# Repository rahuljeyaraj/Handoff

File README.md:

# Handoff

**Shake hands. Share contacts.**

Two people wear a wristband. They shake hands, and their contact cards cross
between the bands **through the two bodies** and land in each other's phones. No
cards, no QR codes, no spelling a name out.

The body is the wire. A coated metal plate on the back of each band couples a
pair of tones into the skin at 180 and 200 kHz, the handshake joins the two
arms, and the plate on the other band picks up what survives. Capacitive
body-coupled communication, at 0 cm.

**[Read the full write-up, with figures](docs/element14-blog.md)** is the place
to start. It is the project end to end: what it feels like to use, how the link
works, the two physical layers, and two appendices that get you from an empty
desk to a working pair.

Built for element14's **Make a Connection** contest. The PCBs were sponsored by
[PCBWay](https://www.pcbway.com/).

---

## What is here

A finished pair of bands, and everything that made them.

| | |
|---|---|
| **Firmware** | `firmware/` one C image per milestone, Pico SDK, host-testable DSP and protocol |
| **Board** | `hardware/` KiCad 10, generated from a script, fabrication zip ready to upload |
| **Box** | `hardware/enclosure/` two printed halves, 22 mm strap |
| **App** | `android/` native Android: pairing, provisioning, history, notes |
| **Docs** | `docs/` the write-up, the design, the radio, bring-up |

## Where to go next

| I want to | Read |
|---|---|
| understand the whole thing | [docs/element14-blog.md](docs/element14-blog.md) |
| build a pair myself | appendices A and B of the same file, then [docs/hardware-bringup.md](docs/hardware-bringup.md) |
| know why the electrical design is what it is | [docs/body-coupled-handshake-design.md](docs/body-coupled-handshake-design.md) |
| know how the radio works today | [docs/link-v2-design.md](docs/link-v2-design.md) |
| know what v1 got wrong, and why it matters | appendix C of the write-up |
| find my way round the firmware | [docs/firmware-architecture.md](docs/firmware-architecture.md) |
| work on the board | [hardware/README.md](hardware/README.md) |
| work on the app | [android/README.md](android/README.md) |

---

## Status

Both bands are built, boxed, worn and working. The link on `main` is **v2**, the
second physical layer. v1 is kept only as appendix C of the write-up, because
its mistakes are the reason v2 looks the way it does.

**Measured**

* Two bands complete handshakes continuously through a real skin path, on their
  own cells, with nothing tethered.
* Worn link test, v2: **1015 good frames, frame error rate 0.163**, against
  v1's 447 and 0.296 on the same bench. About twice as good.
* Bands apart at the same spacing, v1: **nothing gets through**. That is the
  measurement that says the path is the body and not the air.
* Host suite: **25 868 checks**, all green, in a couple of seconds, no hardware.
* Every bring-up step on both boards, with a multimeter. No oscilloscope was
  used anywhere in this project.

**Not measured, and worth saying so**

* Current draw, and so battery life. Both cores run flat out all day and nothing
  sleeps.
* Two bands within about 10 cm complete a handshake with nobody holding either
  of them. That is a near-field leak, not the intent.
* The band has to be on the hand that shakes. The other wrist does not work, and
  nothing in the design says why.

Chapter 7 of the write-up is the full list of what the next pair should do
better.

---

## How the link works, in one screen

| | |
|---|---|
| Tones | 180 kHz and 200 kHz, one on the plate at all times, straight out of a PIO pin |
| Bit | two chips, Manchester: low then high is a 0, high then low is a 1 |
| Rate | 4000 chips a second, so **2000 bits a second** |
| Receiver | ADC free-running at 500 ksps into a DMA ring; core 1 runs five Goertzel filters over every 25 samples |
| Window | 50 us, 20 000 a second, five windows to a chip |
| Decision | which of the two tones was louder. Never how loud |
| Guard bins | 140, 160 and 220 kHz, pitches nobody ever sends, measured through the same body and the same amplifier |
| Presence | the tone against the **median of those three**, by a margin computed from "one false busy a minute". Cell-averaging CFAR, not a tracked floor |
| Sync | no chip count: find the one `00` in the preamble, then check 28 of the 30 transitions around it |
| Frame | fixed size, 156 ms, CRC-16/CCITT. No length field |
| Card | a vCard packed from 169 bytes to 79, cut into frames most important first |
| Rendezvous | every band beacons a nonce, then listens for a random time. Being heard is the touch |
| Turn taking | the band that **heard** sends first, then one frame each, plain round robin |
| Clock | 144 MHz, not the SDK's 150, so both tone periods are a whole even number of cycles |

Not one of those numbers was tuned on the bench. Each comes from a requirement
sentence and arithmetic, and the host suite asserts the arithmetic.

---

## Hardware

| | |
|---|---|
| MCU board | Raspberry Pi Pico 2 W (RP2350 + CYW43439), socketed, not soldered |
| Why RP2350 | RP2040 has a known ADC differential-non-linearity defect |
| Why the W | BLE is the link from the band to its owner's phone |
| Why a Pico at all | PIO makes both tones with no oscillator and no driver chip, and leaves both cores for the work |
| Analogue | MCP6292 dual rail-to-rail op-amp, two stages of x11 |
| Electrodes | two 25 x 25 mm copper-clad squares: the taped skin plate, and an outer one tied to board ground that couples to the room |
| Power | 1S LiPo, about 500 mAh, charged on an off-board TP4056. The Pico's own buck-boost takes the cell from 4.2 V down past 3.0 V |
| Wearer UI | one RGB LED, one coin vibration motor, one button, one slide switch |
| Board | 40 x 62 mm, 2 layers, 1.6 mm. `hardware/build/handoff-pcbway.zip` is ready to upload |
| Box | about 45 x 65 x 25 mm, on a 22 mm strap |

> ### Safety is not optional
>
> **Battery only, both ends, whenever anyone is wearing one.** Never on a
> mains-powered laptop. A tethered reading is also a *wrong* reading: the USB
> lead joins the two bands' grounds through the PC, and that return path is the
> thing under test.
>
> **Every electrode is insulated**, edge to edge, and the skin plate is never
> bare. **Hand to hand only**, and **nobody with a pacemaker or an implanted
> defibrillator.**
>
> The series resistors fitted are **100 kOhm**, which holds the worst-case
> current through a person under **33 uA**, with the insulation on top of that.
> The design document's rule is 1 MOhm, ten times less again, and the silkscreen
> and `hardware/bom.csv` still say so. Appendix B.1 of the write-up is the whole
> justification for the deviation.
>
> Read section 13 of
> [docs/body-coupled-handshake-design.md](docs/body-coupled-handshake-design.md)
> before powering anything on a wrist.

---

## Layout

```
CMakeLists.txt            top level; PICO_BOARD=pico2_w, 144 MHz, handoff_add_app()
pico_sdk_import.cmake     stock SDK bootstrap, from pico-sdk 2.3.1

firmware/
  apps/                   one flashable image per milestone
    blink/                board, toolchain and USB console alive
    txgen/                tone generation, self-measured
    adcbench/             the 500 ksps DMA ring and the Goertzel budget
    loopback/             the whole link inside one chip
    linktest/             one-way link between two boards
    turnaround/           half duplex: how fast a band can swap direction
    afe_sweep/            the analogue front end, characterised alone
    bringup/              the PCB bring-up image, driven by scripts/bringup.py
    handoff/              the real thing, plus the LED, motor and wear logic
  lib/
    dsp/                  Goertzel, the FSK decision, CFAR presence, chip sync
    link/                 Manchester, framing, CRC-16, phone-link chunking
    record/               vCard codec, compact TLV, fragmentation, flash store
    proto/                beacon and rendezvous, the exchange, the carousel
    ui/                   the LED vocabulary and the button
    hal/                  the seam: interfaces and config.h, no code
    hal_pico/             the RP2350 binding: PIO, ADC ring, BLE, flash, IPC
  test/
    host/                 unit tests, channel simulator, two-node protocol sim
    vectors/generated/    from tools/gen_vectors.py, derived, git-ignored
    vectors/captures/     from hardware, committed, replayed forever

scripts/build.py          build and flash the firmware        (Windows + Linux)
scripts/test.py           build and run the host tests        (Windows + Linux)
scripts/bringup.py        the PCB bring-up driver: flash, then LED, motor, TX
scripts/link2.py          one process, two boards' consoles, one timeline
scripts/blelog.py         band readings off two phones by radio, never over USB
tools/                    vector generator, reference vCard codec, plotter, labels
hardware/                 the KiCad project, its generators, the fab zip, the box
android/                  the app. Its own Gradle project
docs/                     design, redesign, bring-up, the write-up and its figures
```

Each app is a directory under `firmware/apps/` whose `CMakeLists.txt` ends in
`handoff_add_app(<target>)`. That wrapper exists because the SDK reads the
`.uf2` path from `ARCHIVE_OUTPUT_DIRECTORY` and the `.elf` path from
`RUNTIME_OUTPUT_DIRECTORY`; setting both keeps every artifact together.

---

## Toolchain

Official Raspberry Pi Pico SDK with CMake and Ninja, not PlatformIO. The
low-level work this project needs is first class in the SDK and second class
everywhere else: PIO tone generation, a free-running ADC at 500 ksps into a DMA
ring, core 1 on five Goertzel filters, BLE over BTstack.

Everything is pinned and lives under `~/.pico-sdk`, deliberately **not** on
PATH:

| Component | Version |
|---|---|
| pico-sdk | 2.3.1 |
| ARM GCC | 15.2.Rel1 (`arm-none-eabi`, 15.2.1) |
| CMake | 4.3.4 |
| Ninja | 1.13.2 |
| picotool | 2.3.1 |

These versions appear in three places that must stay in step: the DO-NOT-EDIT
block in [CMakeLists.txt](CMakeLists.txt), the variables at the top of
[scripts/build.py](scripts/build.py), and the paths in
[.vscode/settings.json](.vscode/settings.json).

**First time on a new machine.** Install the **Raspberry Pi Pico** VS Code
extension (`raspberry-pi.raspberry-pi-pico`), open this folder, and let it
download SDK 2.3.1 when prompted. It populates `~/.pico-sdk` with exactly the
layout above.

## Build

In VS Code, `Ctrl+Shift+B`, or the Pico extension's *Compile Project*. From a
terminal, the same command on Windows and Linux:

```
python scripts/build.py                    # configure + build
python scripts/build.py --clean            # wipe build/ first
python scripts/build.py --flash            # build, then flash over USB
python scripts/build.py --config Release
python scripts/build.py --target handoff   # just one app
python scripts/build.py --help
```

Artifacts land in `build/`: `.uf2`, `.elf`, `.bin`, `.hex`, `.map`, `.dis`.

The script prefers the pinned toolchain under `~/.pico-sdk` and falls back to
whatever is on `PATH`, so a Linux box with distro `cmake`, `ninja` and
`arm-none-eabi-gcc` builds this without the VS Code extension's bundle. Python
3.8 or newer, standard library only.

**For a real band, use the bring-up script instead**, because the PCB moves the
transmitter pin and wants its own build directory:

```
python scripts/bringup.py flash handoff
```

That builds into `build-pcb/` with the board's pin map, flashes it, and can then
drive the LED, the motor and the transmitter from the PC. It is the script
[docs/hardware-bringup.md](docs/hardware-bringup.md) is written against.

## Flash

Either drag a `.uf2` onto the `RP2350` drive that appears when you plug the board
in holding **BOOTSEL**, or use `--flash`. `picotool ... -fx` reboots a running
board into BOOTSEL by itself, so BOOTSEL is only needed for the first flash. On
Linux, install picotool's udev rules rather than running the flash step under
`sudo`.

With two boards on one PC, name the board by its serial rather than its COM
port. The serial is matched as a suffix, so `93D1` finds `4904EF1FFA2393D1`, and
that survives the ports moving.

## Serial console

The firmware presents a USB CDC port. Any terminal at any baud rate works, and
the rate is ignored because it is USB:

```
# Windows: 'mode' lists COM ports; attach with PuTTY or Windows Terminal
# Linux:   /dev/ttyACM0; attach with 'screen /dev/ttyACM0' or 'picocom'
```

For a two-board bench, use `scripts/link2.py` instead of two terminals. It opens
both consoles in one process, stamps every line with the time since the run
started, and can send commands on a schedule. Two separate terminals cannot
answer "which board decided to send first", because their clocks are the
operator's hands.

**Never read a worn band over USB.** Use `scripts/blelog.py`, which takes the
same counters off both phones over BLE while the bands stay floating. A tethered
reading of a body link is wrong, not just unsafe.

---

## Host tests

**Most of this project is testable with no hardware at all**, and that is
structural rather than lucky: nothing under `lib/dsp`, `lib/link`, `lib/record`,
`lib/proto` or `lib/ui` may include a Pico SDK header, so they all compile with a
host compiler and run against a channel simulator.

```
python scripts/test.py                    build and run everything
python scripts/test.py --check            the layering rule only, no compiler
python scripts/test.py --suite frame      one suite
python scripts/test.py --ber              the BER sweep
python scripts/test.py --sweep            the parameter sweeps
python scripts/test.py --define HANDOFF_GZ_N=50
```

A run regenerates the golden vectors from `tools/gen_vectors.py`, cross-checks
the C vCard codec against `tools/vcf.py` in both directions, and executes every
suite. Currently **25 868 checks in a couple of seconds**.

Needs any host C compiler: `gcc` or `clang` if one is on `PATH`, otherwise the
Visual Studio build tools on Windows. This is **separate** from the
`arm-none-eabi` toolchain the firmware uses, and neither substitutes for the
other.

Three rules are worth knowing before changing anything here:

* **Golden vectors are generated from the spec, not from the C encoder**
  (`tools/gen_vectors.py`). If the encoder and decoder share a misreading of the
  frame format, a loopback test passes and the link still fails on the bench. An
  independent generator is the only thing that catches that.
* **Every hardware failure becomes a host test.** A capture that broke the
  decoder on the bench goes into `firmware/test/vectors/captures/` through
  `tools/replay.py --adopt` and is replayed forever. The bug is not fixed until
  it is a regression test.
* **The derived constants are asserted, not trusted.** The tone periods, the
  CFAR margin, the sync threshold and the clock are static-asserted in
  `firmware/lib/hal/config.h` and re-derived in the suite. Changing one number by
  hand fails the build, which is the point.

---

## Two things the design doc gets wrong about the Pico 2 W

Both cost an evening, and both fail silently rather than at build time.

**The SMPS mode pin.** Section 10.4 says tie **GP23** high to force
fixed-frequency PWM. That is right for a plain Pico 2
(`PICO_SMPS_MODE_PIN 23`) and **wrong for the 2 W**: there GP23 drives the CYW43
power enable, and SMPS mode control moves to WL_GPIO1 on the wireless chip,
`cyw43_arch_gpio_put(CYW43_WL_GPIO_SMPS_PIN, true)`.

**The LED.** For the same reason there is no `PICO_DEFAULT_LED_PIN` on a 2 W, so
even blinking needs `cyw43_arch_init()` first.

---

## Thanks

[PCBWay](https://www.pcbway.com/) sponsored and manufactured the boards, and
their engineers caught two real problems in the files before anything was made.
Chapter 9 of the write-up is that story. Thank you to Serene, Tori and Sophia.

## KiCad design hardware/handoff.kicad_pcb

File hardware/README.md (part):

# Handoff — PCB

KiCad 10 project for the wristband board. Companion to
[docs/body-coupled-handshake-design.md](../docs/body-coupled-handshake-design.md);
the schematic implements its §6/§7 netlist with the changes listed under
*Deviations* below.

**Sponsor:** [PCBWay](https://www.pcbway.com/) is fabricating this board.

| File | What |
|---|---|
| `handoff.kicad_pro` / `handoff.kicad_sch` | the project and its single schematic sheet |
| `handoff.kicad_sym` | project symbol library: Pico 2 W and MCP6292 (the stock library has neither) |
| `handoff.pretty/` | project footprints: the SS-12F23G5 slide switch, the 3.4 mm M3 mounting hole with its boss keep-out, and the SOD-123FL diode (KiCad has none) |
| `tools/gen_schematic.py` | **the source of the schematic.** Generates the sheet from the §7 netlist and proves it with `kicad-cli`: ERC, the netlist against `EXPECTED_NETS` pin for pin, and the BOM against the parts table below. Edit this, not the sheet |
| `tools/render.py` | renders `build/handoff.pdf` to `build/sheet.png` so the sheet can be looked at |
| `review.md` | the pre-layout review: every check, its number, its verdict |
| `schematic-prompt.md` | the brief for the next session: the schematic changes the floor plan forces, then layout |
| `tools/gen_sw_footprint.py` | writes `handoff.pretty/SW_Slide_SS-12F23G5`, geometry measured on the physical part |
| `tools/gen_mount_footprint.py` | writes `handoff.pretty/MountingHole_3.4mm_M3_Boss6mm`: 3.4 mm unplated drill plus the 6 mm boss keep-out. The name follows the boss diameter, so the board cannot point at a footprint that is no longer the one described |
| `tools/gen_sod123fl_footprint.py` | writes `handoff.pretty/D_SOD-123FL` for D1/D3, from the PMEG3020ER-TP outline drawing; `--prove` puts it on `build/fp_test.kicad_pcb`, runs DRC and renders it |
| `tools/gen_assembly.py` / `../docs/hardware-bringup/` | the two assembly drawings (each face, fab references, numbered pads, bottom mirrored) that `docs/hardware-bringup.md` is read against |
| `tools/gen_bom.py` / `bom.csv` | the committed BOM: kicad-cli's export plus the **Package** column it cannot produce, derived from each footprint in one place. Called by `gen_schematic.py` after its BOM check |
| `tools/gen_floorplan.py` / `floorplan.svg` | the floor plan: which block sits where in the enclosure, and why. Placement only, no tracks — the **pre-layout** input. **Superseded by the board**: it still draws E1–E10 inboard of their pins, `JP1-JP7`, `TP12`/`TP13` and the 4.5 mm hole positions, none of which exist. Read `gen_pcb.py`'s `PLACE` table for where things actually are |
| `enclosure/` | the box: `bottom.3mf` and `top.3mf`, an initial design, for a 22 mm strap. The board screws into the bottom on four M3 brass inserts |
| `tools/gen_pcb.py` / `handoff.kicad_pcb` | **the source of the board.** Builds it from the schematic's netlist and the floor plan, then proves it with `kicad-cli`: DRC, schematic parity pin for pin, an independent short check, a ground-pour island check, and every pad against every mounting boss. Writes the fab pack last. Edit this, not the `.kicad_pcb` |
| `build/plot/` | the fab pack: Gerbers for every layer, both Excellon drill files with their maps, and the job file. Regenerated on every `gen_pcb.py` run, so it cannot go stale against the board. Not committed (`build/` is ignored) |
| `build/drills.md` | the drill table: every distinct hole, how many, plated or not, and what asks for it |
| `build/handoff-pcbway.zip` / `build/order.md` | **what is actually uploaded.** The zip is the fab pack plus the order sheet; `order.md` is every answer PCBWay's form asks for, written from the board's own numbers, and the list of things to check on their preview. Both regenerated by `gen_pcb.py` |
| `handoff.kicad_dru` | the four custom DRC rules: two tell KiCad about the third dimension it does not model (the Pico is socketed 8.5 mm up; bare pads have no body, but not over a mounting boss), two enforce the layout conventions it will not check unless asked (no right-angle corners, no stub segments). Written by `gen_pcb.py` |

Regenerate and verify after any change (must end `ERC: 0 violation(s), 0 error(s)`,
`0 missing, 0 unexpected` nets, `0 difference(s)` against the parts table, and
`passive packages: 0603` from the BOM writer):

```
python hardware/tools/gen_schematic.py && python hardware/tools/render.py
```

The board is regenerated separately, with KiCad's own Python (it needs `pcbnew`):

```
"C:/Program Files/KiCad/10.0/bin/python.exe" hardware/tools/gen_pcb.py
```

It must end `DRC: 0 error(s)`, `parity 0`, `unrouted 0 item(s)`,
`fab pack: 17 files in build/plot` and `upload pack: build/handoff-pcbway.zip`,
with no `NET`, `OUTSIDE` or `IN BOSS` lines.
Run `gen_schematic.py` first: the board is built from `build/handoff.net`.

---

## Parts — as ordered from robu.in

Every part below is the exact SKU on order. Do not substitute a package
without changing the footprint.

| Ref | Part | Package / mounting | Robu SKU | Qty |
|---|---|---|---|---|
| U1 | Raspberry Pi Pico 2 W | **socketed** in two 1×20 female strips, not soldered to the board | R190344 | 1 |
| — | 2.54 mm 1×40 female single-row header | cut into two 1×20 for the Pico; nothing else uses it now | 555698 | 1 strip |
| U2 | MCP6292-E/MS dual op-amp, 10 MHz | MSOP-8, soldered directly to the board (no DIP adapter on the PCB) | R193529 | 1 |
| R1, R2, R3 | 1 MΩ ±1 % 100 mW 75 V (Uniohm 0603WAF1004T5E) | **0603** | R134792 | 3 |
| R4, R6, R7, R10, R11, R17 | 100 kΩ (104) | **0603** | MakerBazar 1481824519-20P | 6 (pack of 20) |
| R5, R8, R15 | 10 kΩ (103) | **0603** | MakerBazar 1481824531-20P | 3 (pack of 20) |
| R9 | 1.5 kΩ ±1 % 100 mW 75 V (Uniohm 0603WAF1501T5E) | **0603** | R134878 | 1 |
| R12, R13, R14, R16 | 100 Ω (101) | **0603** | MakerBazar 1860310035-20P | 4 (pack of 20) |
| C3 | 100 nF X7R ±10 % 50 V (Samsung CL10B104KB8NNNC) | **0603** | R172322 | 1 |
| C1, C2 | 330 pF **C0G/NP0** ±5 % 100 V (Samsung CL10C331JC8NNNC) | **0603** | R136892 | 2 |
| C4, C5 | 10 µF X5R ±20 % **25 V** (Murata GRM188R61E106MA73D) | **0603**, non-polarised | R144171 | 2 |
| C6 | **DNP** — 330 pF C0G, the C2 part, fitted only if GP11 leakage turns out to matter (see *Deviations*) | **0603** | R136892 | 0 |
| D1 | PMEG3020ER-TP (**Tech Public**), SOD-123FL, 40 V 2 A Schottky — *not* the Nexperia PMEG3020ER, which is SOD-123W | **SOD-123FL**, `handoff:D_SOD-123FL` | R241663 | 1 |
| SW1 | SS-12F23G5 slide switch, SPDT (1P2T), right-angle, 5 mm handle | 3 terminals at 3.0 mm pitch + 2 mounting ears, `handoff:SW_Slide_SS-12F23G5` | R132611 | 1 |
| D2 | RGB LED, common cathode, 5 mm, clear (5-pack) | off-board: solders into J3 or plugs in via a 4-pin XH pigtail | R183455 | 1 |
| SW2 | Tactile push button 6 × 6 × 5 mm, 4 legs | through-hole, `Button_Switch_THT:SW_PUSH_6mm` | 618182 | 1 |
| Q1 | AO3400A N-channel MOSFET, 30 V 5.2 A, 27 mΩ @ 4.5 V | SOT-23 | MakerBazar R209179 | 1 |
| D3 | PMEG3020ER-TP (**Tech Public**), SOD-123FL, 40 V 2 A Schottky, motor flyback — the D1 part | **SOD-123FL**, `handoff:D_SOD-123FL` | R241663 | 1 |
| M1 | Coin vibration motor, 1034, 10 mm disc, ~3 V | off-board: leads solder into J6 | MakerBazar 522260 | 1 |
| J6 | Motor pads, 2 × 2.54 mm through-hole | takes the motor leads direct, or a 2-pin header | — | 1 |
| J1 | JST-XH 2.54 straight 2-pin male (battery) | through-hole | — | 1 |
| J5 | JST-XH 2.54 straight 2-pin male (charger — **one more 2-pin header than before**) | through-hole | — | 1 |
| J2 | JST-XH 2.54 straight 2-pin male (electrodes) | through-hole | — | 1 |
| J3 | JST-XH 2.54 straight 4-pin male (LED), or the LED soldered straight in | through-hole | — | 1 |
| BT1 | 502030 Li-ion 3.7 V 500 mAh | off-board, on a JST-XH pigtail | — | 1 |

Copper only, nothing to buy: 8 solder jumpers JP1–JP8, 8 test pads TP1–TP8, and
4 mounting holes H1–H4 (M3 clearance, 3.4 mm, unplated, each with a 6 mm boss
keep-out).

The 10 MΩ (Robu 574992) bought for R3 is no longer fitted — see *Deviations*. Keep
it: it is the A/B part for the M7 recovery-versus-loss comparison.

**Every passive on the board is 0603** since the 12 Sep 2026 order (see the last
*This session*). The 1206 1 MΩ / 1.5 kΩ / 330 pF / 100 nF (574983, R137563,
R111869, R153721) and the 0805 10 µF (MakerBazar 1491785836-10P) are no longer
fitted anywhere, and nor is the SS220F (Slkor R193098) both diodes were.

Not on the board, by decision: the TP4056 charger (the cell is charged off-board)
and the MSOP-to-DIP adapter (perfboard only).

> JST "XH" is a 2.50 mm pitch family, not 2.54. Over four pins the difference is
> 0.12 mm and the footprint holes absorb it, so the 5 mm LED's 2.54 mm legs go
> straight into J3.

---

## Deviations from the design doc, and why

**D1 in series with VSYS.** The Pico datasheet's own recommendation for a board
that is battery powered but still gets plugged into USB for flashing: the Pico's
internal Schottky ORs VBUS into VSYS, and this external one stops VSYS from
back-driving the battery. It also makes a reversed battery plug harmless (nothing
powers up) instead of destructive. **Now PMEG3020ER-TP (Tech Public, 40 V 2 A,
SOD-123FL)**, the third part in this position after the 1N5819 (DO-41) and the
SS220F (SMB) — see the session logs. Cost: **~0.4 V at 100 mA** (0.41 V typ at
1 A, 0.5 V max at 2 A, from the Tech Public datasheet; its Fig. 4 puts 100 mA at
0.35–0.4 V — there is no 100 mA line item), leaving ~2.9–3.8 V on VSYS from a
3.3–4.2 V cell, against the Pico's 1.8–5.5 V input range. That is 0.45 V better
than the SS220F's ~0.85 V, which was the price of a 200 V rating this board never
needed. Reverse leakage is 2 µA at 10 V, 25 °C.

**A haptic motor was added, on VSYS behind an N-FET.** Not in the design
doc at all — it arrived with this session's parts order. M1 is off-board on
leads into J6; Q1 switches it low-side from GP28, D3 catches the flyback,
R16/R17 are the gate chain. It runs from VSYS rather than the Pico's 3V3
regulator so that 100 mA of pulsed motor current never shares a rail with
the analogue front end. See *This session* below.

**Battery polarity on J1: pin 1 = BAT−, pin 2 = BAT+.** There is no universal
convention for a 2-pin JST battery plug; the one real XH convention is the
balance-lead one, where pin 1 (square pad) is the negative end. The silkscreen
will say so. Verify the pigtail against the silkscreen before the first plug-in —
D1 means getting it wrong costs nothing but a re-pinned plug.

**RGB LED on GP17 / GP18 / GP19 (R / G / B) through 330 Ω.** J3 pin order is
R, K, G, B — the lead order of a standard 5 mm common-cathode RGB LED, longest
leg second — so the LED can be soldered directly. At 3.3 V and 330 Ω the red
runs ~4 mA and green/blue ~1 mA: a status indicator, not a torch.

*Moved one pin up from GP16/17/18 by the floor plan.* J3 sits hard against the
thumb-side edge, parallel to it, opposite the Pico's **thumb row — which is pins
21–40**, not 1–20. With R → GP17 (pin 22), K → GND (pin 23), G → GP18 (pin 24),
B → GP19 (pin 25), J3's four pins face pins 22–25 straight across: four ~7 mm
traces, no crossings, and the LED's legs bend 90° straight into the header with
no pigtail. The cathode lands on a Pico GND pin that is already there, so the
LED's return does not travel.

**Which row is which.** The Pico sits at 180°: USB overhanging the elbow edge
puts the antenna keep-out at the hand end, and it puts **pins 1–20 on the
little-finger row and pins 21–40 on the thumb row.** The floor plan had these
mirrored until the layout session checked the footprint's own pad coordinates
against its USB and antenna zones. Everything that names a Pico pin and a board
position — J3, the TX escape, BTN and ROLE — depends on
getting this right; it is the cheapest thing on the board to verify and the most
expensive to get wrong.

**J2 carries both electrodes: pin 1 = PAD, pin 2 = ground-plane electrode.**
The ground plane does *not* need air contact; it needs area and distance from
the PAD. Inside a box, the board's own ground pour (plus the Pico's) already is a
ground plane facing outward. J2 pin 2 exists so a separate copper-clad sheet can
be added on the outer face of the enclosure — design §15.1 — if measurement
shows the board's pour is too small. Exactly one wire, per §8.4; the connector
is that one point.

**Solder jumpers, all normally OPEN.** Two copper pads 0.3 mm apart, no part;
bridge with a solder blob to connect, wick it off to isolate. Open rather than
cut-to-open because a blob is reversible and a knife cut is not. The price:
**the board does nothing as delivered until the in-line jumpers are bridged**,
which is deliberate — nothing on this board has been tested, so every stage can
be isolated and driven from a test pad on its own. An open jumper is two
separate nets in the netlist oracle.

| | in series with | open, it isolates… | …and the isolated side is driven from | first used |
|---|---|---|---|---|
| JP5 | D1 cathode → VSYS | the whole board from the cell (USB still powers it) | an ammeter across JP5's own two pads reads the board current; a bench supply on pad 2 replaces the cell | M3 bring-up, M11 battery life |
| JP4 | 3V3 → U2 VDD (and the VREF divider) | the analogue side from the Pico's rail | a bench supply / second cell on JP4 pad 2 — the SMPS-noise experiment; an ammeter across JP4 reads U2's current | M7 |
| JP6 | R10/R11/C4 divider → VREF | the bias divider from the amplifiers | an external 1.65 V on JP6 pad 2 | M7 if VREF is suspected |
| JP7 | PAD → R2 | the pad and the transmitter from the receiver | a signal generator on JP7 pad 2 (through R2: the 1 MΩ is still in circuit) | M7 gain / corner / clipping sweeps |
| JP2 | GP11 → R1 | the transmitter from the pad | nothing — leave open and fit C6 instead if GP11 leakage biases the pad (moving TX to another GPIO does not help: every bank-0 pin has E9) | M3 (measure leakage first), M8 |
| JP3 (3-way) | OUT1 / OUT2 → R9 | the ADC from both stages; centre pad → R9, pad 3 ← OUT2 (×121), pad 1 ← OUT1 (×11) | JP3's own pad 3 or pad 1 as a bare output for the scope | M7: blob to pad 3; move it to pad 1 if a noisy hall clips stage 2 (design §15.2) |
| JP1 | R9 → GP26/ADC0 | the ADC pin from the amplifier | JP1 pad 2 directly, as M5 does with its own attenuator; a wire from JP1 pad 2 to any Pico GND pin grounds the ADC for the M4 noise floor | M4/M5 open, M7 bridged |
| JP8 | GP14 → GND | (a strap, not in-line) | — | M6: bridge on one board to set its role; firmware enables GP14's pull-up |

Nothing touches the high-impedance node (R2/R3/U2 pin 3): no jumper, no test
pad. JP7
is on the *pad* side of R2.

**Bring-up order** — the sequence that makes the jumpers pay for themselves:

1. Nothing bridged, no cell. USB in: the Pico runs, M3–M5 need nothing else
   (M5's loopback goes JP2 pad 1 → JP1 pad 2 by wire; JP1 pad 2 to a Pico GND
   pin grounds the ADC for M4).
2. Bridge **JP4** and **JP6**. Read 3.3 V on JP4 pad 2, 1.65 V ±5 % on JP6
   pad 2, 1.65 V on JP3 pads 1 and 3. Anything else on JP3 is a bias problem:
   open JP6 and inject 1.65 V on its pad 2 to split divider from amplifier.
3. Bridge **JP3 centre–pad 3**. Inject on JP7 pad 2 (JP7 still open): gain,
   corner, clipping and noise sweeps of M7, reading JP3 pad 3 with a scope and
   the ADC after bridging **JP1**.
4. Bridge **JP7**. Now the pad is live; M8 with a capacitor from J2 pin 1 to a
   Pico GND pin.
5. Bridge **JP2** *only after* the M3 leakage measurement (below) says the
   pad node stays at 1.65 V with GP11 high-Z. If it does not, fit **C6** instead.
6. Bridge **JP5** last, with the cell on J1; first reading of J1 pin 2 against
   JP5 pad 2 is the D1 drop.

**There are no test pads.** There were thirteen; every one of them sat on the
same net as a solder-jumper pad, a connector pin or a Pico header pin two
millimetres away, and the owner probes with a meter or a scope tip rather than
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
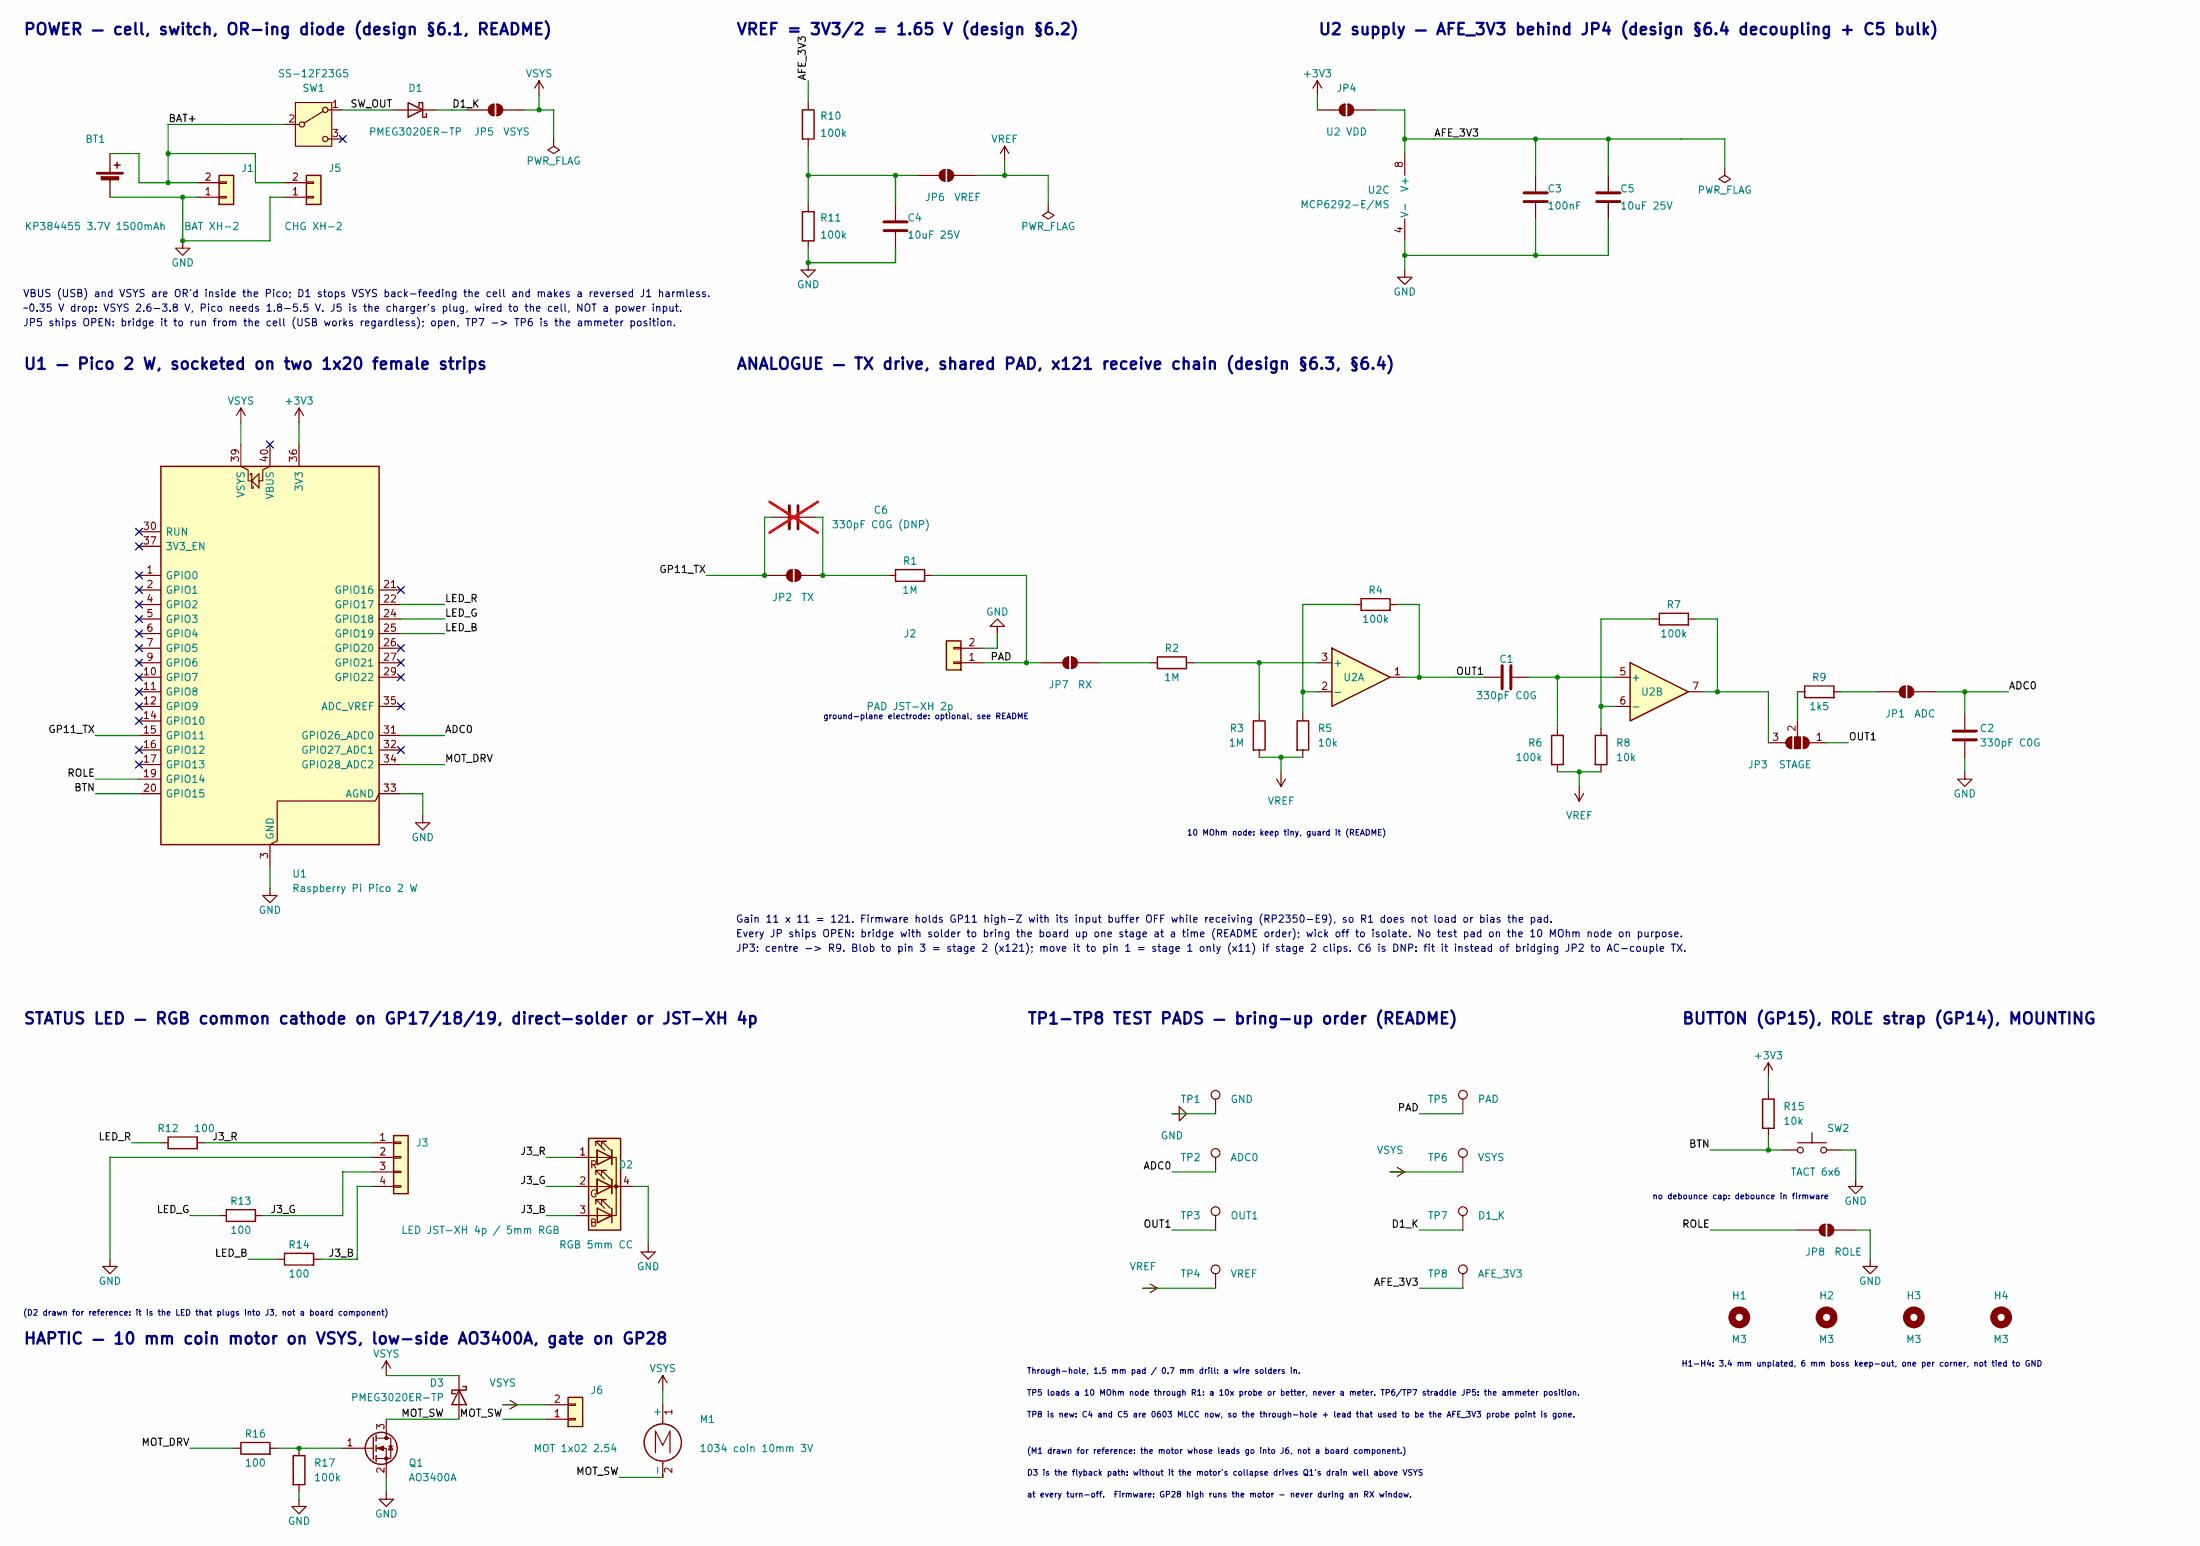
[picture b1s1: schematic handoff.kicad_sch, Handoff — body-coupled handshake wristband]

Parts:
BT1: KP384455 3.7V 1500mAh
C1, C2: 330pF C0G; C_0603_1608Metric_Pad1.08x0.95mm_HandSolder
C3: 100nF; C_0603_1608Metric_Pad1.08x0.95mm_HandSolder
C4, C5: 10uF 25V; C_0603_1608Metric_Pad1.08x0.95mm_HandSolder
C6: 330pF C0G (DNP); C_0603_1608Metric_Pad1.08x0.95mm_HandSolder; not fitted
D1, D3: PMEG3020ER-TP; D_SOD-123FL
D2: RGB 5mm CC
H1, H2, H3, H4: M3; MountingHole_3.4mm_M3_Boss6mm
J1: BAT XH-2; JST_XH_B2B-XH-A_1x02_P2.50mm_Vertical
J2: PAD JST-XH 2p; JST_XH_B2B-XH-A_1x02_P2.50mm_Vertical
J3: LED JST-XH 4p / 5mm RGB; JST_XH_B4B-XH-A_1x04_P2.50mm_Vertical
J5: CHG XH-2; JST_XH_B2B-XH-A_1x02_P2.50mm_Vertical
J6: MOT 1x02 2.54; PinHeader_1x02_P2.54mm_Vertical
JP1: ADC; SolderJumper-2_P1.3mm_Open_RoundedPad1.0x1.5mm
JP2: TX; SolderJumper-2_P1.3mm_Open_RoundedPad1.0x1.5mm
JP3: STAGE; SolderJumper-3_P1.3mm_Open_RoundedPad1.0x1.5mm
JP4: U2 VDD; SolderJumper-2_P1.3mm_Open_RoundedPad1.0x1.5mm
JP5: VSYS; SolderJumper-2_P1.3mm_Open_RoundedPad1.0x1.5mm
JP6: VREF; SolderJumper-2_P1.3mm_Open_RoundedPad1.0x1.5mm
JP7: RX; SolderJumper-2_P1.3mm_Open_RoundedPad1.0x1.5mm
JP8: ROLE; SolderJumper-2_P1.3mm_Open_RoundedPad1.0x1.5mm
M1: 1034 coin 10mm 3V
Q1: AO3400A; SOT-23
R1, R2, R3: 1M; R_0603_1608Metric_Pad0.98x0.95mm_HandSolder
R4, R6, R7, R10, R11, R17: 100k; R_0603_1608Metric_Pad0.98x0.95mm_HandSolder
R5, R8, R15: 10k; R_0603_1608Metric_Pad0.98x0.95mm_HandSolder
R9: 1k5; R_0603_1608Metric_Pad0.98x0.95mm_HandSolder
R12, R13, R14, R16: 100; R_0603_1608Metric_Pad0.98x0.95mm_HandSolder
SW1: SS-12F23G5; SW_Slide_SS-12F23G5
SW2: TACT 6x6; SW_PUSH_6mm
TP1: GND; TestPoint_THTPad_D1.5mm_Drill0.7mm
TP2: ADC0; TestPoint_THTPad_D1.5mm_Drill0.7mm
TP3: OUT1; TestPoint_THTPad_D1.5mm_Drill0.7mm
TP4: VREF; TestPoint_THTPad_D1.5mm_Drill0.7mm
TP5: PAD; TestPoint_THTPad_D1.5mm_Drill0.7mm
TP6: VSYS; TestPoint_THTPad_D1.5mm_Drill0.7mm
TP7: D1_K; TestPoint_THTPad_D1.5mm_Drill0.7mm
TP8: AFE_3V3; TestPoint_THTPad_D1.5mm_Drill0.7mm
U1: Raspberry Pi Pico 2 W; RaspberryPi_Pico_Common_THT
U2: MCP6292-E/MS; MSOP-8_3x3mm_P0.65mm

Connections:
+3V3: JP4.1 (A), R15.1, U1.36 (3V3)
/ADC0: C2.1, JP1.2 (B), TP2.1, U1.31 (GPIO26_ADC0)
/AFE_3V3: C3.1, C5.1, JP4.2 (B), R10.1, TP8.1, U2.8 (V+)
/BAT+: BT1.1 (+), J1.2, J5.2, SW1.2 (B)
/BTN: R15.2, SW2.1, U1.20 (GPIO15)
/D1_K: D1.1 (K), JP5.1 (A), TP7.1
/GP11_TX: C6.1, JP2.1 (A), U1.15 (GPIO11)
/J3_B: D2.3 (BA), J3.4, R14.2
/J3_G: D2.2 (GA), J3.3, R13.2
/J3_R: D2.1 (RA), J3.1, R12.2
/LED_B: R14.1, U1.25 (GPIO19)
/LED_G: R13.1, U1.24 (GPIO18)
/LED_R: R12.1, U1.22 (GPIO17)
/MOT_DRV: R16.1, U1.34 (GPIO28_ADC2)
/MOT_SW: D3.2 (A), J6.1, M1.2 (-), Q1.3 (D)
/OUT1: C1.1, JP3.1 (A), R4.2, TP3.1, U2.1
/PAD: J2.1, JP7.1 (A), R1.2, TP5.1
/ROLE: JP8.1 (A), U1.19 (GPIO14)
/SW_OUT: D1.2 (A), SW1.1 (A)
GND: BT1.2 (-), C2.2, C3.2, C4.2, C5.2, D2.4 (K), J1.1, J2.2, J3.2, J5.1, JP8.2 (B), Q1.2 (S), R11.2, R17.2, SW2.2, TP1.1, U1.3 (GND), U1.8 (GND), U1.13 (GND), U1.18 (GND), U1.23 (GND), U1.28 (GND), U1.33 (AGND), U1.38 (GND), U2.4 (V-)
unnamed: JP1.1 (A), R9.2
unnamed: C6.2, JP2.2 (B), R1.1
unnamed: JP3.3 (B), R7.2, U2.7
unnamed: JP3.2 (C), R9.1
unnamed: C4.1, JP6.1 (A), R10.2, R11.1
unnamed: JP7.2 (B), R2.1
unnamed: Q1.1 (G), R16.2, R17.1
unnamed: R2.2, R3.1, U2.3 (+)
unnamed: R4.1, R5.1, U2.2 (-)
unnamed: C1.2, R6.1, U2.5 (+)
unnamed: R7.1, R8.1, U2.6 (-)
VREF: JP6.2 (B), R3.2, R5.2, R6.2, R8.2, TP4.1
VSYS: D3.1 (K), J6.2, JP5.2 (B), M1.1 (+), TP6.1, U1.39 (VSYS)

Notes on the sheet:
POWER — cell, switch, OR-ing diode (design §6.1, README)
VBUS (USB) and VSYS are OR'd inside the Pico; D1 stops VSYS back-feeding the cell and makes a reversed J1 harmless.
~0.35 V drop: VSYS 2.6-3.8 V, Pico needs 1.8-5.5 V. J5 is the charger's plug, wired to the cell, NOT a power input.
JP5 ships OPEN: bridge it to run from the cell (USB works regardless); open, TP7 -> TP6 is the ammeter position.
VREF = 3V3/2 = 1.65 V (design §6.2)
U2 supply — AFE_3V3 behind JP4 (design §6.4 decoupling + C5 bulk)
U1 — Pico 2 W, socketed on two 1x20 female strips
ANALOGUE — TX drive, shared PAD, x121 receive chain (design §6.3, §6.4)
ground-plane electrode: optional, see README
10 MOhm node: keep tiny, guard it (README)
Gain 11 x 11 = 121. Firmware holds GP11 high-Z with its input buffer OFF while receiving (RP2350-E9), so R1 does not load or bias the pad.
Every JP ships OPEN: bridge with solder to bring the board up one stage at a time (README order); wick off to isolate. No test pad on the 10 MOhm node on purpose.
JP3: centre -> R9. Blob to pin 3 = stage 2 (x121); move it to pin 1 = stage 1 only (x11) if stage 2 clips. C6 is DNP: fit it instead of bridging JP2 to AC-couple TX.
STATUS LED — RGB common cathode on GP17/18/19, direct-solder or JST-XH 4p
(D2 drawn for reference: it is the LED that plugs into J3, not a board component)
TP1-TP8 TEST PADS — bring-up order (README)
Through-hole, 1.5 mm pad / 0.7 mm drill: a wire solders in.
TP5 loads a 10 MOhm node through R1: a 10x probe or better, never a meter. TP6/TP7 straddle JP5: the ammeter position.
TP8 is new: C4 and C5 are 0603 MLCC now, so the through-hole + lead that used to be the AFE_3V3 probe point is gone.
BUTTON (GP15), ROLE strap (GP14), MOUNTING
no debounce cap: debounce in firmware
H1-H4: 3.4 mm unplated, 6 mm boss keep-out, one per corner, not tied to GND
HAPTIC — 10 mm coin motor on VSYS, low-side AO3400A, gate on GP28
(M1 drawn for reference: the motor whose leads go into J6, not a board component.)
D3 is the flyback path: without it the motor's collapse drives Q1's drain well above VSYS
at every turn-off. Firmware: GP28 high runs the motor - never during an RX window.

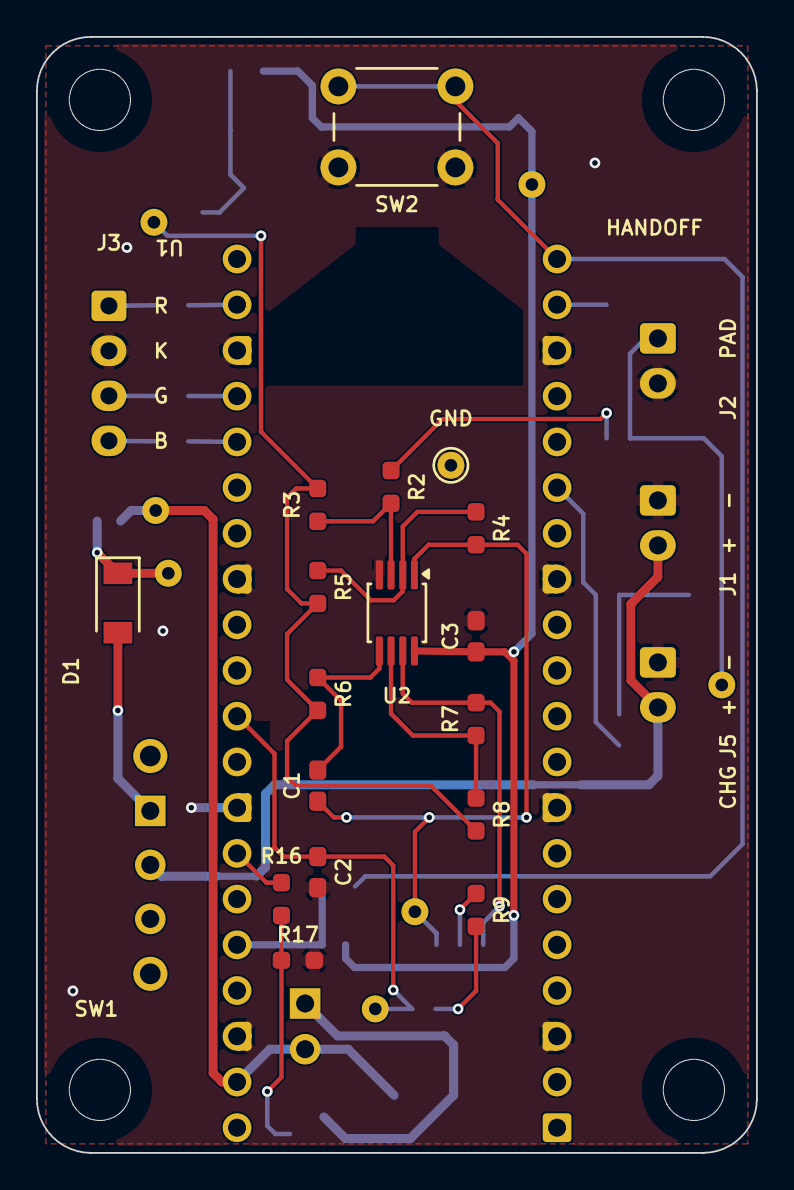
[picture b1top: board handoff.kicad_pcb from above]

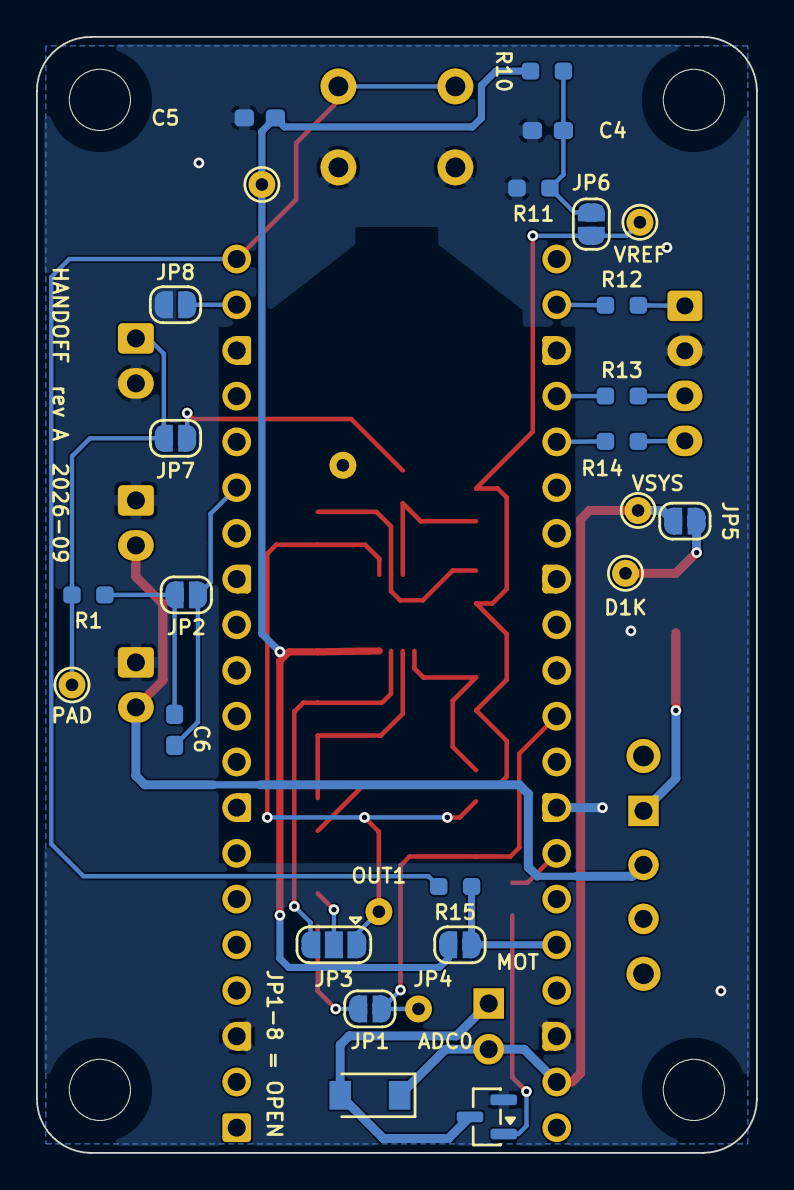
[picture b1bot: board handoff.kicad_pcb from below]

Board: 2 copper layers, 40.0 x 62.0 mm, 55 parts (28 on the bottom side), 33 nets.

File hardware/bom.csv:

"Reference","Qty","Value","Package","Footprint","Description","DNP"
"BT1","1","KP384455 3.7V 1500mAh","Off-board, on a JST-XH pigtail","","Li-ion cell, off-board, on a JST-XH pigtail",""
"C1,C2","2","330pF C0G","0603","Capacitor_SMD:C_0603_1608Metric_Pad1.08x0.95mm_HandSolder","Anti-alias, 321 kHz with R9,Interstage DC block",""
"C3","1","100nF","0603","Capacitor_SMD:C_0603_1608Metric_Pad1.08x0.95mm_HandSolder","U2 decoupling, across pins 8 and 4",""
"C4,C5","2","10uF 25V","0603","Capacitor_SMD:C_0603_1608Metric_Pad1.08x0.95mm_HandSolder","U2 bulk decoupling against the Pico SMPS, X5R 0603,VREF hold-up, X5R 0603",""
"C6","1","330pF C0G (DNP)","0603","Capacitor_SMD:C_0603_1608Metric_Pad1.08x0.95mm_HandSolder","DNP. Optional TX DC block in parallel with JP2; fit instead of bridging JP2 if GP11 leakage biases the pad","DNP"
"D1,D3","2","PMEG3020ER-TP","SOD-123FL","handoff:D_SOD-123FL","Motor flyback, Schottky 40 V 2 A, SOD-123FL (Tech Public, not Nexperia),VSYS OR-ing / reverse polarity, Schottky 40 V 2 A, SOD-123FL (Tech Public, not Nexperia)",""
"D2","1","RGB 5mm CC","Off-board: solders into J3, or plugs in via a 4-pin XH pigtail","","Off-board LED, plugs into / solders into J3",""
"J1","1","BAT XH-2","THT, JST-XH 2.50 mm, 2-pin","Connector_JST:JST_XH_B2B-XH-A_1x02_P2.50mm_Vertical","Battery input, JST-XH 2p. Pin 1 = BAT-, pin 2 = BAT+",""
"J2","1","PAD JST-XH 2p","THT, JST-XH 2.50 mm, 2-pin","Connector_JST:JST_XH_B2B-XH-A_1x02_P2.50mm_Vertical","Pin 1 = skin PAD, pin 2 = ground-plane electrode (optional)",""
"J3","1","LED JST-XH 4p / 5mm RGB","THT, JST-XH 2.50 mm, 4-pin","Connector_JST:JST_XH_B4B-XH-A_1x04_P2.50mm_Vertical","Pin order R, K, G, B = 5 mm common-cathode RGB LED leads",""
"J5","1","CHG XH-2","THT, JST-XH 2.50 mm, 2-pin","Connector_JST:JST_XH_B2B-XH-A_1x02_P2.50mm_Vertical","Charger port, JST-XH 2p, parallel to J1: TP4056 OUT- to pin 1, OUT+ to pin 2. Not a power input",""
"J6","1","MOT 1x02 2.54","THT, 2.54 mm pin header, 2-pin","Connector_PinHeader_2.54mm:PinHeader_1x02_P2.54mm_Vertical","Motor, 2 x 2.54 mm THT. Pin 1 = MOT_SW (switched), pin 2 = VSYS",""
"M1","1","1034 coin 10mm 3V","Off-board: leads solder into J6","","Coin vibration motor, off-board, leads into J6",""
"Q1","1","AO3400A","SOT-23","Package_TO_SOT_SMD:SOT-23","Low-side motor switch, N-channel 30 V / 5.2 A, 27 mOhm at 4.5 V, SOT-23",""
"R1,R2,R3","3","1M","0603","Resistor_SMD:R_0603_1608Metric_Pad0.98x0.95mm_HandSolder","Biases the 10 MOhm node to VREF,RX safety resistor, design §13,TX safety resistor, design §13",""
"R4,R6,R7,R10,R11,R17","6","100k","0603","Resistor_SMD:R_0603_1608Metric_Pad0.98x0.95mm_HandSolder","Q1 gate pull-down: holds the motor off while GP28 is an input,Re-bias stage 2 +IN to VREF,Stage 1 feedback,Stage 2 feedback,VREF divider, bottom,VREF divider, top",""
"R5,R8,R15","3","10k","0603","Resistor_SMD:R_0603_1608Metric_Pad0.98x0.95mm_HandSolder","BTN pull-up,Stage 1 gain set: 1 + R4/R5 = 11,Stage 2 gain set: 1 + R7/R8 = 11",""
"R9","1","1k5","0603","Resistor_SMD:R_0603_1608Metric_Pad0.98x0.95mm_HandSolder","ADC series / anti-alias with C2",""
"R12,R13,R14,R16","4","100","0603","Resistor_SMD:R_0603_1608Metric_Pad0.98x0.95mm_HandSolder","LED B series,LED G series,LED R series,Q1 gate series",""
"SW1","1","SS-12F23G5","THT, SS-12F23G5 slide switch (right-angle SPDT)","handoff:SW_Slide_SS-12F23G5","Power switch, SPDT slide, right angle",""
"SW2","1","TACT 6x6","THT, 6x6 mm tactile button","Button_Switch_THT:SW_PUSH_6mm","Bench control: force TX / force RX / provisioning / clear bond. Pads 1-1 and 2-2 are the switch's internally joined pairs",""
"U1","1","Raspberry Pi Pico 2 W","THT, socketed (2x 1x20 female headers), not soldered","Module:RaspberryPi_Pico_Common_THT","",""
"U2","1","MCP6292-E/MS","MSOP-8 (3x3 mm, 0.65 mm pitch)","Package_SO:MSOP-8_3x3mm_P0.65mm","",""

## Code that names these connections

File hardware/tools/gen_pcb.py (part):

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    "SW1": ("2", 6.3, 46.0, 270, TOP),
    # D1 and JP5 sit between J3 and SW1, so the whole battery path lives on
    # the thumb wall: BAT+ crosses the board once (J1 to SW1), SW_OUT is a
    # 7 mm hop from SW1's pin 1 to D1's anode, and VSYS runs down the lane
    # between the breakout pads and the pin row straight into pin 39, which
    # is on this row. On the little-finger side, where they were, the path
    # crossed the board three times and threaded the pin rows six times.
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    # so pin 3 (+IN A) faces open board. R2 sits directly in line with it and R3
    # beside them: the island is pin 3 + two pads, and nothing else touches it.
    "U2":  ("@", 20.0, 32.0, 270, TOP),
    # R2 sits in line with pin 3, as far toward U2 as the slot above U2's pad
    # row allows: pin 2's escape north (x 20.325, mitred at y 27.7) and pin 1's
    # both live in that slot, and R2's pad 2 has to stay 0.2 mm above them. As
    # a 1206 that put R2 at y 24.0 (pad 2 at 25.55); as an 0603 it is at 25.0,
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    # pin 3 - is 8.5 mm of trace now, 9.2 before: the shorter parts give it
    # back, and it stays an island: nothing else routes through the space the
    # 1206 bodies left.
    "R2":  ("@", 19.675, 25.0, 270, TOP),   # pad 1 RX_IN north, pad 2 (HIZ) south, in line with pin 3
    "R3":  ("@", COL_L, 26.0, 90, TOP),     # pad 1 (HIZ) south at y 26.9125, pad 2 VREF north

    # left column: stage-1 feedback, the interstage pair, the ADC cap
    "R5":  ("@", COL_L, 30.5625, 270, TOP),  # FB1 pad on 29.65, where the 1206 put it
    "R6":  ("@", COL_L, 36.5, 270, TOP),    # IN2 pad 2.5 mm from pin 5
    # The VREF bus crosses this column at y 41.6, UNDER C1, between its two
    # pads. A 1206 left 1.32 mm for it; an 0603 leaves 0.775, which is a 0.25
    # track with 0.2625 to each pad - so C1's origin sits exactly on the bus
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    "C2":  ("1", COL_L, 45.538, 270, TOP),  # pad 1 ADC0 north, pad 2 GND

    # right column. The hand-end slot is deliberately empty: it is the only band
    # in which the pad-side nets can cross the Pico's pin row on the top layer.
    "R4":  ("@", COL_R, 27.3, 270, TOP),    # OUT1 pad 2.5 mm from pin 1
    # C3's supply pad is 3.4 mm from pin 8 and its ground pad returns through
    # the pour to pin 4, which is the diagonally opposite corner of the
    # package. The slot above (R4) is what lets pins 1 and 2 out and the slot
    # below (R7) is what lets 6 and 7 out; turning C3 flat would block one
    # row's fan-out. 3.4 mm of 0.4 mm track on a 100 nF at a 10 MHz op-amp
    # is the loop the package allows. Anchored on that supply pad, so the
    # AFE_3V3 lane (x 26.5, from this pad's y) did not move when C3 went 0603.
    "C3":  ("1", COL_R, 34.163, 90, TOP),   # pad 1 AFE_3V3 south, on pin 8's row; pad 2 GND north
    # R7 at 90, not 270: it puts OUT2 (pad 2) above FB2 (pad 1), which is the
    # order pins 7 and 6 leave U2 in. The other way round the two nets have to
    # cross, and on a two-layer board with a pour on both sides that costs vias
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    # J1, J2 and J5 are through-hole: their pads occupy x 33.65-35.35 on THIS
    # face too, in three bands across it. Everything here goes in the gaps
    # between those bands, or outboard of them.
    "JP8": ("@", 32.3, 14.88, 180, BOT),    # ROLE, in line with pin 19
    "JP7": ("@", 32.3, 22.3, 0, BOT),       # between J2's band and J1's; pad 1 PAD east
    # JP2 and R1 sit in line between J1's band and J5's: GP11 arrives from the
    # west, PAD leaves at the wall. R1 is anchored on its PAD pad, which is the
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    "C6":  ("@", 32.35, 38.5, 90, BOT),     # DNP across JP2: pad 2 north on JP2.2's x, pad 1 south
    # R15 is the BTN pull-up. It sits at the elbow end because +3V3 is on the
    # elbow end of the thumb row (pin 36): the rail crosses the channel once,
    # at the elbow, and the long run up the wall to pin 20 is the static BTN
    # line at 0.25 mm, not the Pico's switching rail beside the receive node.
    # It lies under the Pico, in the band between the pocket and the jumper
    # pads (y 47.2), with pad 1 straight above JP4's +3V3 pad on x 15.85: the
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    # ---- the elbow block ------------------------------------------------
    # Three solder jumpers now (JP6 went to the hand end with its divider).
    # JP4 and JP3 sit on y 50.44, pin 36's row, so +3V3 runs straight out of
    # the pin into JP4's pad; each jumper is turned so the pad faces the net
    # that feeds it.
    "JP4": ("@", 16.5, 50.44, 180, BOT),   # pad 1 +3V3 west, pad 2 AFE_3V3 east
    "JP3": ("@", 23.5, 50.44, 180, BOT),   # pad 1 OUT1 west, pads 2/3 to R9/R7
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    # ---- haptic: the motor driver, bottom face at the thumb end of the elbow
    # This is the only free ground left on the board: x 12-18 between the Pico's
    # thumb pin row and JP1, below JP4. It is also the right place electrically -
    # VSYS arrives at pin 39 (11.12, 58.06), two millimetres away, so the motor's
    # 100 mA pulses never travel the length of the board, and it is 10 mm of
    # board and a ground pour away from the AFE channel.
    # J6's holes sit at x 14.9, not on the Pico's own pin lane: the gate has to
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
ROUTES = [
    # ---- the LED, straight across the thumb strip on the bottom face ------
    ("/LED_R", BL, [pico_pin(22), P("R12", "1")]),
    ("/LED_G", BL, [pico_pin(24), P("R13", "1")]),
    ("/LED_B", BL, [pico_pin(25), P("R14", "1")]),
    ("/J3_R", BL, [(4.0, 14.94), P("R12", "2")]),
    ("/J3_G", BL, [(4.0, 19.94), P("R13", "2")]),
    ("/J3_B", BL, [(4.0, 22.44), P("R14", "2")]),
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    # ---- the battery path, all on the thumb wall ---------------------------
    # BAT+: J1 to J5 on the top face (the connector pins are through-hole, so
    # no via), jogging round J5's ground pin; then down the bottom face from
    # J5, through C6's pad gap, across the whole channel between pins 8/9 and
    # 33/34 (BAT+ is the only track on this band), and into SW1's common from
    # the east. It enters pin 2 from the east so that pin 1's north side is
    # free for SW_OUT to leave.
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                   (12.7, Y_BATP_TH - 0.5), (12.2, Y_BATP_TH)]),
    ("/BAT+", BL, [(12.2, Y_BATP_TH), (10.0, Y_BATP_TH)], NECK),
    ("/BAT+", BL, [(10.0, Y_BATP_TH), (6.93, Y_BATP_TH), (6.3, 46.0)]),
    # SW_OUT: pin 1 north-west, past the switch's mounting ear, into D1's anode.
    # D1 is SMD now (SMB then, SOD-123FL now), F.Cu only: the old bend point becomes a via and a
    # short F.Cu stub continues straight on to the pad (still x = 4.5, so the
    # via-to-pad leg is collinear with the B.Cu leg above it, not a corner).
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    # D1's cathode to JP5, and JP5 to VSYS. VSYS goes through TP6 to the top
    # face, threads between E7 and E8, and runs the lane between the breakout
    # pads and the pin row (0.97 mm: 0.28 mm each side of a 0.5 mm track)
    # straight down into pin 39 from the north-west. D1's cathode (pad 1) is
    # also F.Cu only: JP5's branch's old 45-degree bend point becomes a via,
    # with a short F.Cu stub on into the pad at the same 45, so the angle at
    # the via is unchanged (135 degrees, same as it always was at the pad).
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                  (X_VSYS, 58.06 - 0.49), (X_VSYS + 0.49, 58.06), pico_pin(39)]),

    # ---- ROLE and BTN ------------------------------------------------------
    ("/ROLE", BL, [pico_pin(19), (31.65, 14.88)]),
    # BTN: out of R15 with one 45 onto pin 6/7's gap, through it, up the
    # little-finger wall on the bottom face (a static line, 0.25 mm, 0.68 mm
    # from the edge), west along pin 20's row into the pin, then on the top
    # face to SW2. Off pin 20 it leaves at 45 straight out of the pad: the
    # 45 passes TP8 (27.5, 8.2) at 1.9 mm, where a stub north first put it
    # at 1.2, one clearance off the pad. The jog to x 25.6 is for SW2's
    # ground pad at (23.25, 7.25), which a 45 all the way would run through.
    ("/BTN", BL, [P("R15", "2"), P("R15", "2", 0.57, -0.57), (37.4125, Y_BTN_LF),
                  (39.2, 44.8425), (39.2, 13.34), (38.2, 12.34), pico_pin(20)]),
    ("/BTN", TL, [pico_pin(20), (25.6, 9.04), (25.6, 5.9),
                  (23.25, 3.55), (23.25, 2.75)]),
    ("/BTN", BL, [(16.75, 2.75), (23.25, 2.75)]),    # SW2's two pad-1s

    # ---- TX: GP11 -> JP2 -> R1 -> PAD, all on the little-finger strip -----
    ("/GP11_TX", BL, [pico_pin(15), (30.35, 26.49), (30.35, 30.3), (31.05, 31.0)]),
    # C6 (DNP) hangs off JP2's two pads: pad 2 straight down from JP2.2, pad 1
    # down from JP2.1 with one 45 at the bottom
    ("/GP11_TX", BL, [P("JP2", "1"), P("C6", "1", -1.3, -1.3), P("C6", "1")]),
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    ("Net-(U2A-+)", TL, [P("R3", "1"), P("R2", "2", -1.0, 1.0), P("R2", "2")]),

    # ---- stage 1 -----------------------------------------------------------
    # Pin 2 leaves its pad twice: north into the slot above the pad row, and
    # south under U2's body, where the island's vertical does not reach. Each
    # is one straight leg and one 45 onto the resistor's pad row.
    ("Net-(U2A--)", TL, [P("U2", "2"), P("R4", "1", -4.075, 0.8125), P("R4", "1", -3.2625), P("R4", "1")]),
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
